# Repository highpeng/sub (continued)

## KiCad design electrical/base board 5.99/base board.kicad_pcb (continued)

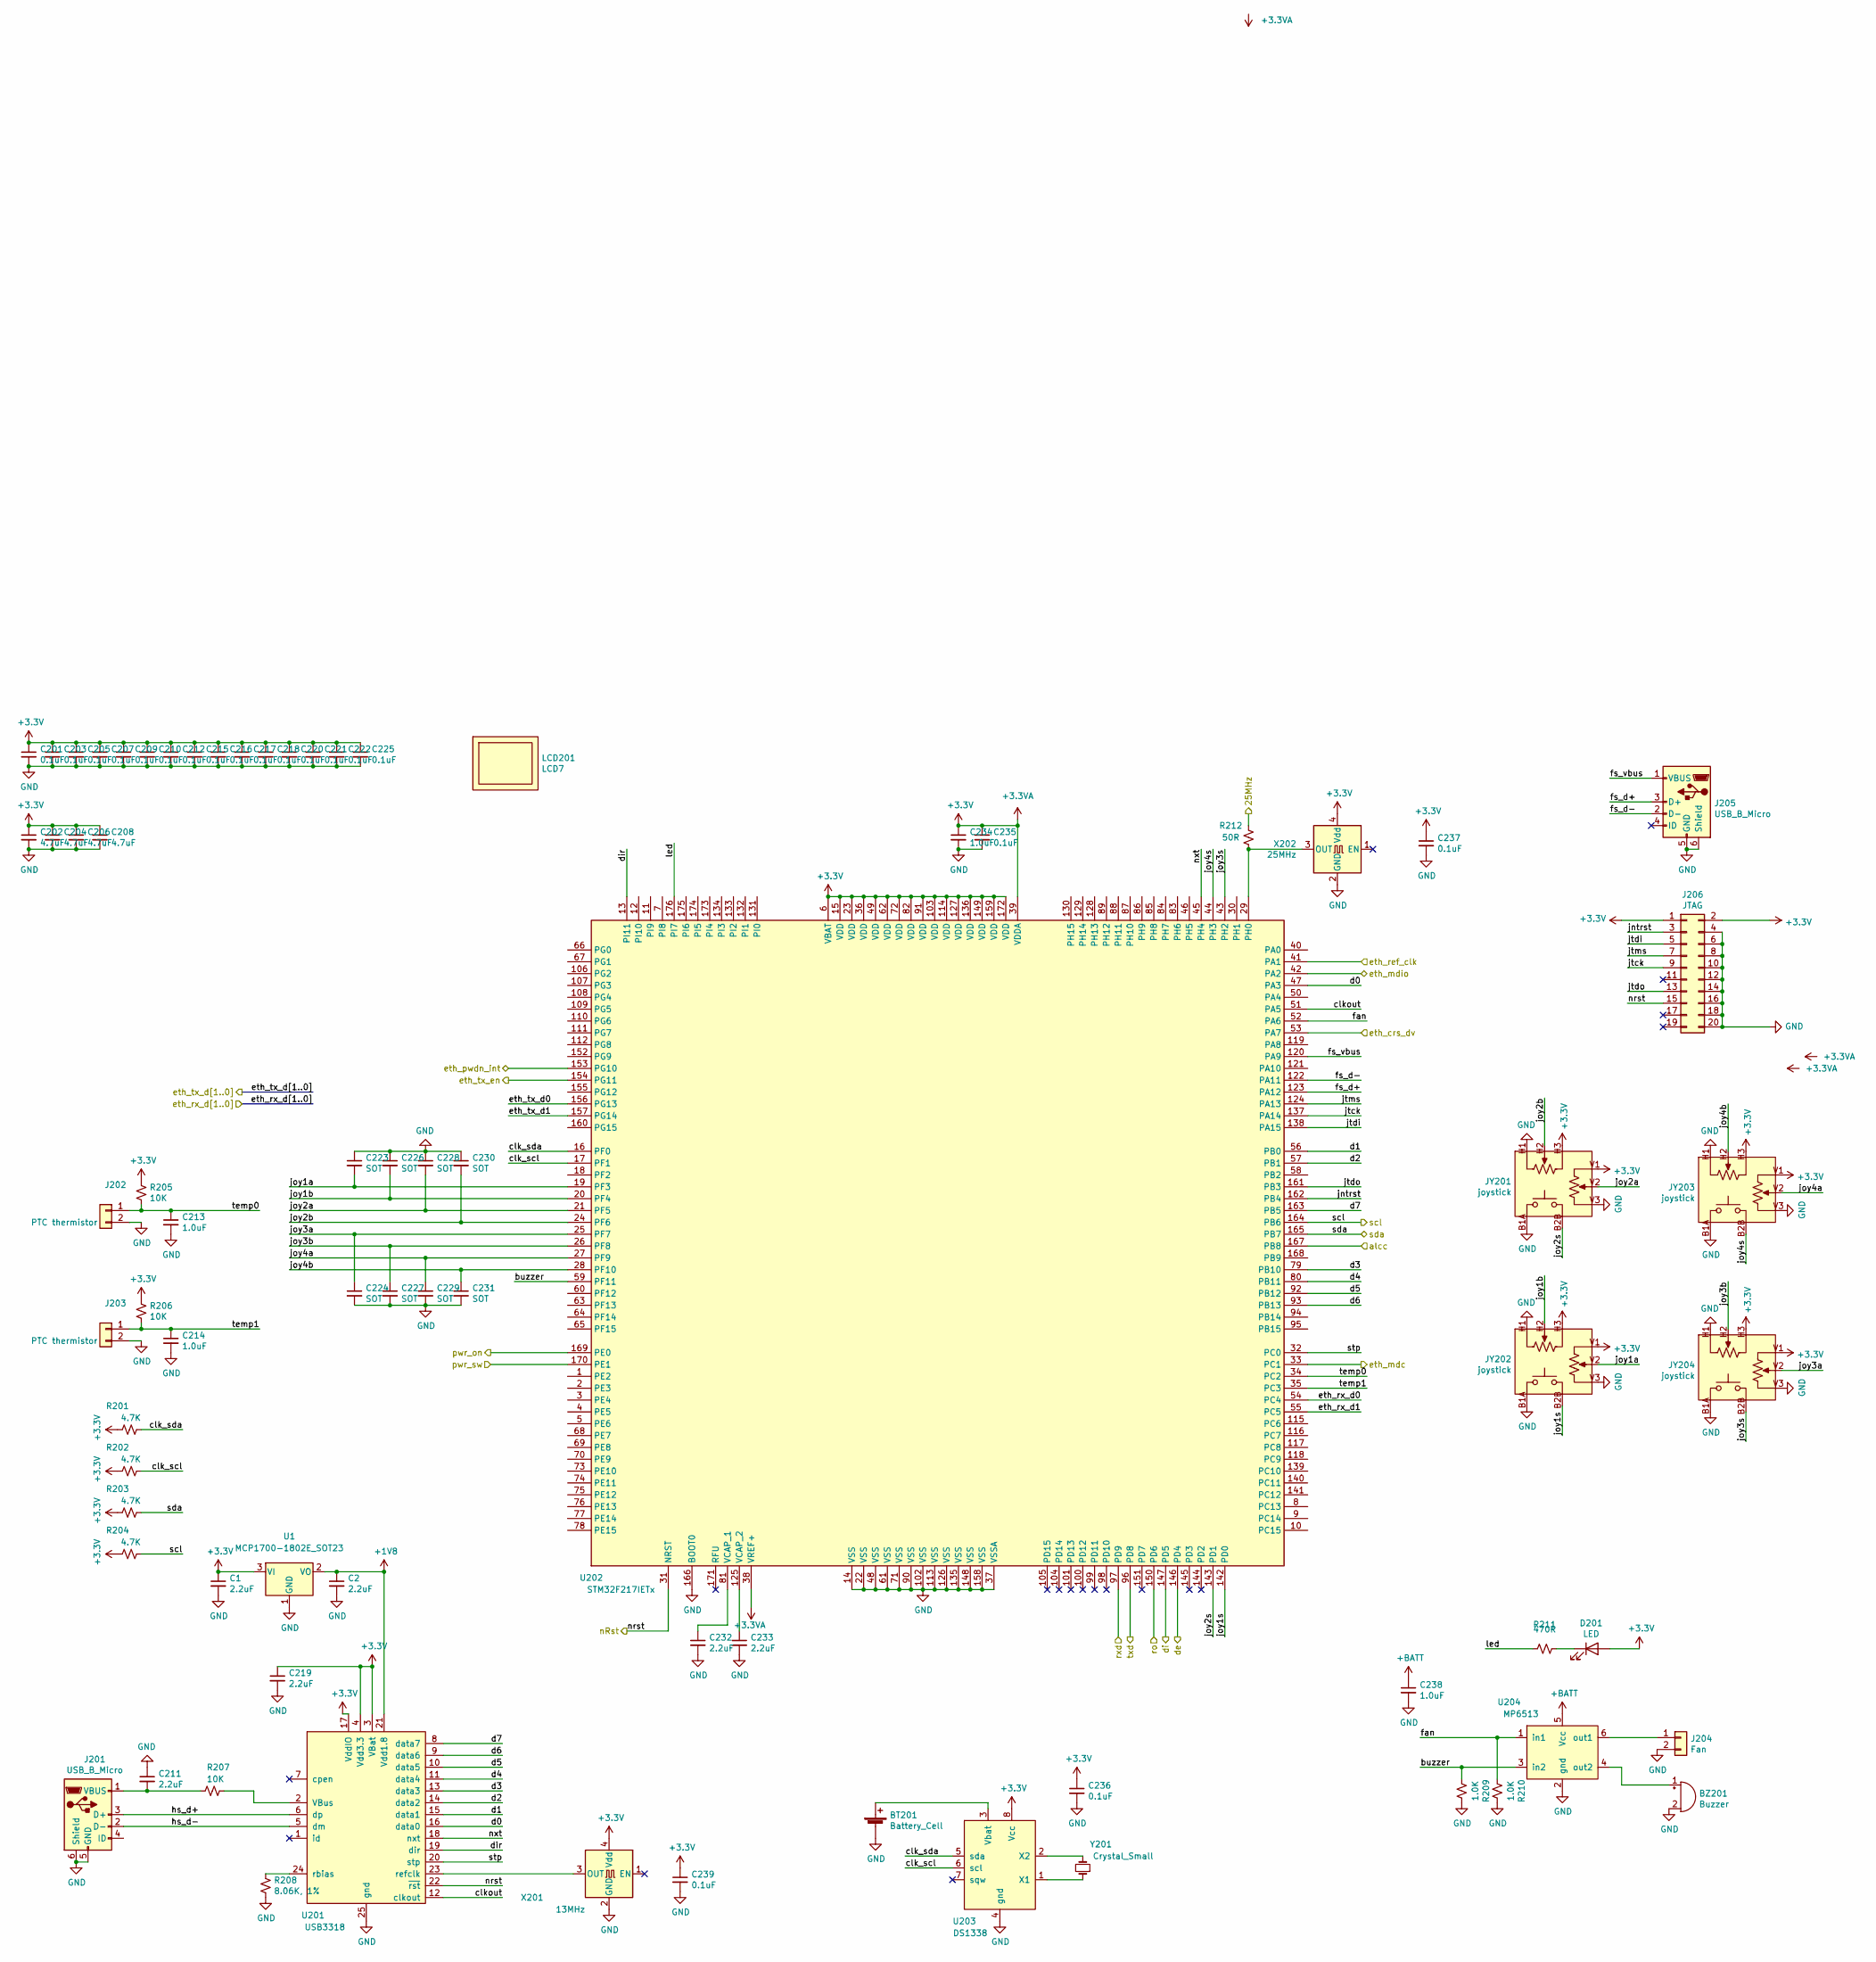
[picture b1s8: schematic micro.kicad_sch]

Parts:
BT201: Battery_Cell; BH-49C-1-BK
BZ201: Buzzer; CPI-1375-80T
C1, C2, C211, C219, C232, C233: 2.2uF; C_0603_1608Metric
C201, C203, C205, C207, C209, C210, C212, C215, C216, C217, C218, C220, C221, C222, C225, C235, C236, C237, C239: 0.1uF; C_0402_1005Metric
C202, C204, C206, C208: 4.7uF; C_0603_1608Metric
C213, C214, C234, C238: 1.0uF; C_0603_1608Metric
C223, C224, C226, C227, C228, C229, C230, C231: SOT; C_0402_1005Metric
D201: LED; LED_0402_1005Metric
J201, J205: USB_B_Micro; USB_Micro-B_Wuerth_629105150521
J202, J203: PTC thermistor; Hirose_DF13C_CL535-0402-2-51_1x02-1MP_P1.25mm_Vertical
J204: Fan; Hirose_DF13C_CL535-0402-2-51_1x02-1MP_P1.25mm_Vertical
J206: JTAG; IDC-Header_2x10_P2.54mm_Vertical
JY201, JY202, JY203, JY204: joystick; XDCR_COM-09032
LCD201: LCD7
R201, R202, R203, R204: 4.7K; R_0402_1005Metric
R205, R206, R207: 10K; R_0402_1005Metric
R208: 8.06K, 1%; R_0402_1005Metric
R209, R210: 1.0K; R_0402_1005Metric
R211: 470R; R_0402_1005Metric
R212: 50R; R_0402_1005Metric
U1: MCP1700-1802E_SOT23; SOT-23
U201: USB3318; QFN-24-1EP_4x4mm_P0.5mm_EP2.6x2.6mm
U202: STM32F217IETx; LQFP-176_24x24mm_P0.5mm
U203: DS1338; SOIC-8_3.9x4.9mm_P1.27mm
U204: MP6513; TSOT-23-6
X201: 13MHz; 831056290
X202: 25MHz; ASFL1
Y201: Crystal_Small; CMJ206T

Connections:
+1V8: C2.1, U1.2 (VO), U201.21 (Vdd1.8)
+3V3: C1.1, C201.1, C202.1, C203.1, C204.1, C205.1, C206.1, C207.1, C208.1, C209.1, C210.1, C212.1, C215.1, C216.1, C217.1, C218.1, C219.1, C220.1, C221.1, C222.1, C225.1, C234.1, C235.1, C236.1, C237.1, C239.1, D201.2 (A), J206.1, J206.2, JY201.H3, JY201.V1, JY202.H3, JY202.V1, JY203.H3, JY203.V1, JY204.H3, JY204.V1, R201.1, R202.1, R203.1, R204.1, R205.1, R206.1, U1.3 (VI), U201.3 (VBat~), U201.4 (Vdd3.3), U201.17 (VddIO), U202.6 (VBAT), U202.15 (VDD), U202.23 (VDD), U202.36 (VDD), U202.38 (VREF+), U202.39 (VDDA), U202.49 (VDD), U202.62 (VDD), U202.72 (VDD), U202.82 (VDD), U202.91 (VDD), U202.103 (VDD), U202.114 (VDD), U202.127 (VDD), U202.136 (VDD), U202.149 (VDD), U202.159 (VDD), U202.172 (VDD), U203.8 (Vcc), X201.4 (Vdd), X202.4 (Vdd); also elsewhere on the board
+BATT: C238.1, U204.5 (Vcc); also elsewhere on the board
/RS485/DE: U202.146 (PD4); also elsewhere on the board
/RS485/DI: U202.147 (PD5); also elsewhere on the board
/RS485/RO: U202.150 (PD6); also elsewhere on the board
/RaspberryPI_CM4/rxd: U202.96 (PD8); also elsewhere on the board
/RaspberryPI_CM4/txd: U202.97 (PD9); also elsewhere on the board
/battery/alcc: U202.167 (PB8); also elsewhere on the board
/battery/pwr_sw: U202.170 (PE1); also elsewhere on the board
/battery/scl: R204.2, U202.164 (PB6); also elsewhere on the board
/battery/sda: R203.2, U202.165 (PB7); also elsewhere on the board
/battery/st_pwr_en: U202.169 (PE0); also elsewhere on the board
/ethernet/25MHz: R212.2; also elsewhere on the board
/ethernet/50MHz: U202.41 (PA1); also elsewhere on the board
/ethernet/crs_dv: U202.53 (PA7); also elsewhere on the board
/ethernet/mdc: U202.33 (PC1); also elsewhere on the board
/ethernet/mdio: U202.42 (PA2); also elsewhere on the board
/ethernet/pwdn_int: U202.153 (PG10); also elsewhere on the board
/ethernet/tx_en: U202.154 (PG11); also elsewhere on the board
/micro/buzzer: R209.2, U202.59 (PF11), U204.3 (in2)
/micro/clk_scl: R202.2, U202.17 (PF1), U203.6 (scl)
/micro/clk_sda: R201.2, U202.16 (PF0), U203.5 (sda)
/micro/clkout: U201.12 (clkout), U202.51 (PA5)
/micro/d0: U201.16 (data0), U202.47 (PA3)
/micro/d1: U201.15 (data1), U202.56 (PB0)
/micro/d2: U201.14 (data2), U202.57 (PB1)
/micro/d3: U201.13 (data3), U202.79 (PB10)
/micro/d4: U201.11 (data4), U202.80 (PB11)
/micro/d5: U201.10 (data5), U202.92 (PB12)
/micro/d6: U201.9 (data6), U202.93 (PB13)
/micro/d7: U201.8 (data7), U202.163 (PB5)
/micro/dir: U201.19 (dir), U202.13 (PI11)
/micro/eth_rx_d0: U202.54 (PC4); also elsewhere on the board
/micro/eth_rx_d1: U202.55 (PC5); also elsewhere on the board
/micro/eth_tx_d0: U202.156 (PG13); also elsewhere on the board
/micro/eth_tx_d1: U202.157 (PG14); also elsewhere on the board
/micro/fan: R210.2, U202.52 (PA6), U204.1 (in1)
/micro/fs_d+: J205.3 (D+), U202.123 (PA12)
/micro/fs_d-: J205.2 (D-), U202.122 (PA11)
/micro/fs_vbus: J205.1 (VBUS), U202.120 (PA9)
/micro/hs_d+: J201.3 (D+), U201.6 (dp)
/micro/hs_d-: J201.2 (D-), U201.5 (dm)
/micro/jntrst: J206.3, U202.162 (PB4)
/micro/joy1a: C223.2, JY202.V2, U202.19 (PF3)
/micro/joy1b: C226.2, JY202.H2, U202.20 (PF4)
/micro/joy1s: JY202.B2B, U202.142 (PD0)
/micro/joy2a: C228.2, JY201.V2, U202.21 (PF5)
/micro/joy2b: C230.2, JY201.H2, U202.24 (PF6)
/micro/joy2s: JY201.B2B, U202.143 (PD1)
/micro/joy3a: C224.1, JY204.V2, U202.25 (PF7)
/micro/joy3b: C227.1, JY204.H2, U202.26 (PF8)
/micro/joy3s: JY204.B2B, U202.43 (PH2)
/micro/joy4a: C229.1, JY203.V2, U202.27 (PF9)
/micro/joy4b: C231.1, JY203.H2, U202.28 (PF10)
/micro/joy4s: JY203.B2B, U202.44 (PH3)
/micro/jtck: J206.9, U202.137 (PA14)
/micro/jtdi: J206.5, U202.138 (PA15)
/micro/jtdo: J206.13, U202.161 (PB3)
/micro/jtms: J206.7, U202.124 (PA13)
/micro/led: R211.2, U202.176 (PI7)
/micro/nrst: J206.15, U201.22 (~rst), U202.31 (NRST); also elsewhere on the board
/micro/nxt: U201.18 (nxt), U202.45 (PH4)
/micro/stp: U201.20 (stp), U202.32 (PC0)
/micro/temp0: C213.1, J202.1, R205.2, U202.34 (PC2)
/micro/temp1: C214.1, J203.1, R206.2, U202.35 (PC3)
GND: BT201.2 (-), BZ201.2 (+), C1.2, C2.2, C201.2, C202.2, C203.2, C204.2, C205.2, C206.2, C207.2, C208.2, C209.2, C210.2, C211.1, C212.2, C213.2, C214.2, C215.2, C216.2, C217.2, C218.2, C219.2, C220.2, C221.2, C222.2, C223.1, C224.2, C225.2, C226.1, C227.2, C228.1, C229.2, C230.1, C231.2, C232.2, C233.2, C234.2, C235.2, C236.2, C237.2, C238.2, C239.2, J201.5 (GND), J201.6 (Shield), J202.2, J203.2, J204.2, J205.5 (GND), J205.6 (Shield), J206.4, J206.6, J206.8, J206.10, J206.12, J206.14, J206.16, J206.18, J206.20, JY201.B1A, JY201.H1, JY201.V3, JY202.B1A, JY202.H1, JY202.V3, JY203.B1A, JY203.H1, JY203.V3, JY204.B1A, JY204.H1, JY204.V3, R208.1, R209.1, R210.1, U1.1 (GND), U201.25 (gnd), U202.14 (VSS), U202.22 (VSS), U202.37 (VSSA), U202.48 (VSS), U202.61 (VSS), U202.71 (VSS), U202.90 (VSS), U202.102 (VSS), U202.113 (VSS), U202.126 (VSS), U202.135 (VSS), U202.148 (VSS), U202.158 (VSS), U202.166 (BOOT0), U203.4 (gnd), U204.2 (gnd), X201.2 (GND), X202.2 (GND); also elsewhere on the board
unnamed: BT201.1 (+), U203.3 (Vbat)
unnamed: BZ201.1 (-), U204.4 (out2)
unnamed: C211.2, J201.1 (VBUS), R207.2
unnamed: C232.1, U202.81 (VCAP_1)
unnamed: C233.1, U202.125 (VCAP_2)
unnamed: J204.1, U204.6 (out1)
unnamed: R207.1, U201.2 (VBus)
unnamed: R208.2, U201.24 (rbias)
unnamed: D201.1 (K), R211.1
unnamed: R212.1, U202.29 (PH0), X202.3 (OUT)
unnamed: U201.23 (refclk), X201.3 (OUT)
unnamed: U203.1 (X1), Y201.1
unnamed: U203.2 (X2), Y201.2

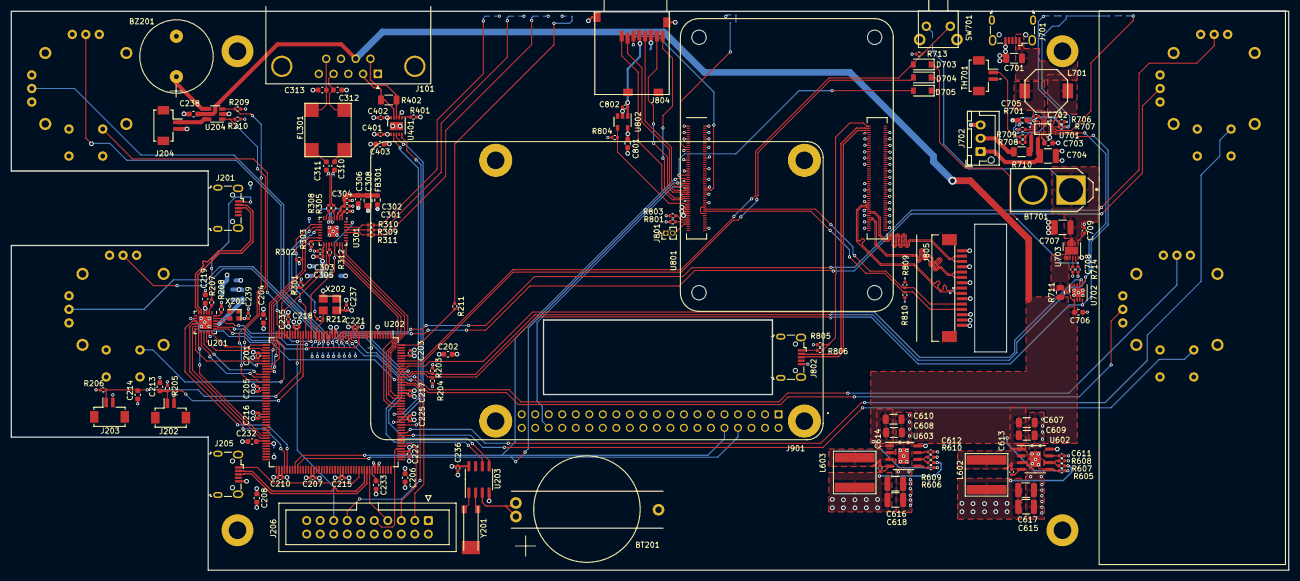
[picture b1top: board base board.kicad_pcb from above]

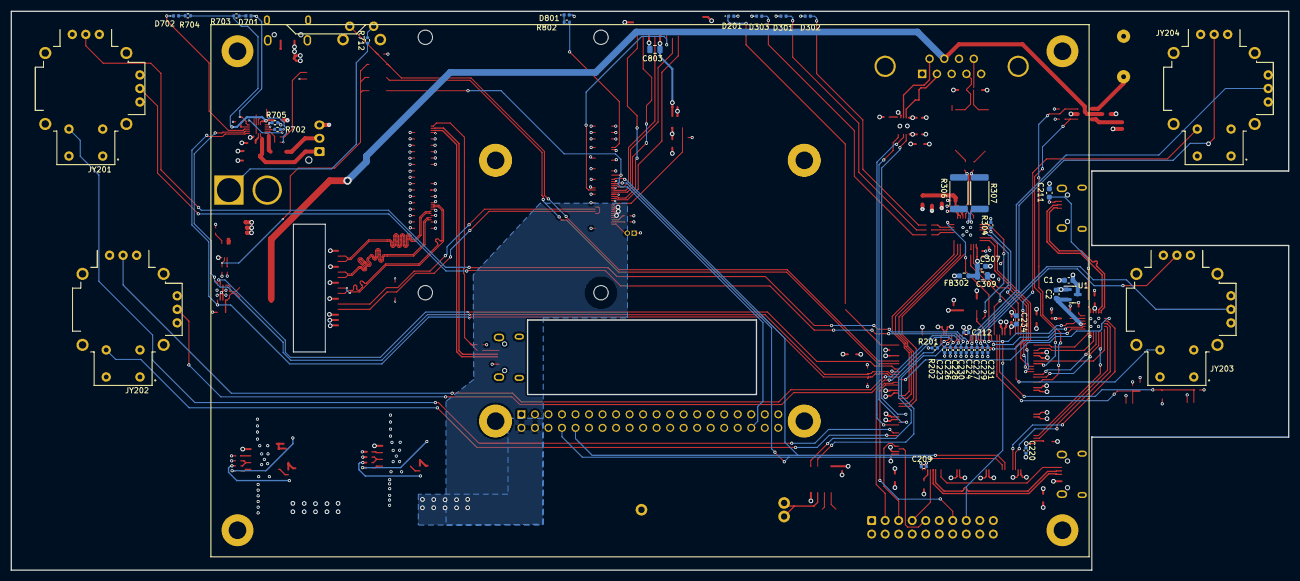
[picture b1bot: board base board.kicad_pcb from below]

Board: 4 copper layers, 240.0 x 105.0 mm, 193 parts (43 on the bottom side), 164 nets.

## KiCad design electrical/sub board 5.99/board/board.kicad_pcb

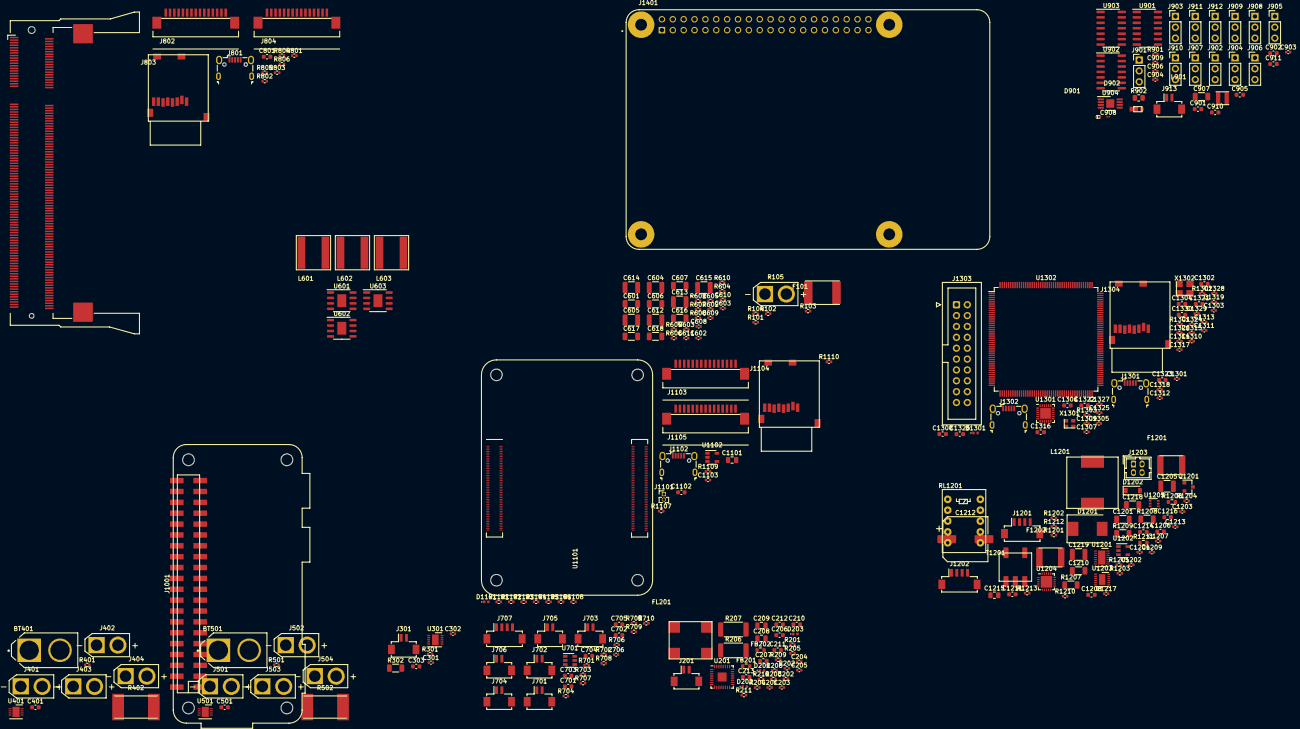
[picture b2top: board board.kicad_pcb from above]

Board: 2 copper layers, 279 parts (0 on the bottom side), 260 nets, no tracks yet.

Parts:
BT401, BT501: Battery; AMASS_XT60-M
C201, C202, C203, C909: 10nF, 16V; C_0402_1005Metric
C204, C205, C301, C302, C602, C603, C608, C609, C610, C611, C706, C903, C904, C906, C1103, C1202, C1301, C1303, C1305, C1307, C1309, C1310, C1311, C1312, C1313, C1314, C1315, C1317, C1318, C1319, C1320, C1324, C1325, C1327, C1328, C1329: 0.1uF; C_0402_1005Metric
C206, C207, C303, C705, C801, C901, C902, C905, C1206, C1208, C1302, C1304, C1306, C1308, C1330: 4.7uF; C_0603_1608Metric
C208, C209, C1101: 10uF; C_0805_2012Metric
C210, C211: 220nF,16V; C_0603_1608Metric
C212, C213: 100pF, 50V; C_0603_1608Metric
C401, C501, C701, C702, C703, C704, C910, C911, C1102, C1323: 1.0uF, 16V; C_0603_1608Metric
C601, C606, C607, C616, C617, C618, C907, C1201, C1218: 10uF,25V; C_1206_3216Metric
C604, C605, C612, C613, C614, C615: 22uF; C_1210_3225Metric
C908: 0.1uF,25V; C_01005_0402Metric
C1203: 33nF; C_0402_1005Metric
C1204, C1213: 6.8nF; C_0402_1005Metric
C1205, C1219: 10uF, 63V, X7R; C_1210_3225Metric
C1207, C1209: 1nF; C_0402_1005Metric
C1210: 0.1uF, 63V; C_1206_3216Metric
C1211, C1214: SOT; C_0603_1608Metric
C1212: 100uF, 63V; CP_MS10
C1215: 330pF, 100V; R_0805_2012Metric
C1216: NIP; C_0603_1608Metric
C1217: SOT; C_0402_1005Metric
C1316, C1321, C1322, C1326: 2.2uF; C_0603_1608Metric
D201, D202, D203, D1101, D1301: LED; LED_0402_1005Metric
D901: RB720M-30; SOD-923
D902: 30V, 1A; DO-219AD
D1201: 50V,4A; D_SMC
D1202: 1N4148; D_SOD-123
F101: 6A; 2920L
F1201, F1202: 3A; 2016
FB201, FB202: FB; R_0603_1608Metric
FL201: 2.2mH; L_WE_SL5
J201: Ethernet; Hirose_DF13C_CL535-0402-2-51_1x02-1MP_P1.25mm_Vertical
J301: RS485; Hirose_DF13C_CL535-0402-2-51_1x02-1MP_P1.25mm_Vertical
J401, J402, J403, J404, J501, J502, J503, J504: thruster_esc; AMASS_XT30U-F_1x02_P5.0mm_Vertical
J701, J702, J703, J704: PTC thermistor; Hirose_DF13C_CL535-0402-2-51_1x02-1MP_P1.25mm_Vertical
J705: water sensor0; Hirose_DF13C_CL535-0402-2-51_1x02-1MP_P1.25mm_Vertical
J706: water sensor1; Hirose_DF13C_CL535-0402-2-51_1x02-1MP_P1.25mm_Vertical
J707: IMU; Hirose_DF13C_CL535-0404-8-51_1x04-1MP_P1.25mm_Vertical
J801, J1102, J1301, J1302: USB_B_Micro; USB_Micro-B_Wuerth_629105150521
J802, J1103: Cam0; Molex_200528-0150_1x15-1MP_P1.00mm_Horizontal
J803, J1104, J1304: Micro_SD_Card_Det; MEM2061
J804, J1105: Cam1; Molex_200528-0150_1x15-1MP_P1.00mm_Horizontal
J901: thruster_esc0; PinHeader_1x03_P2.54mm_Vertical
J902: thruster_esc1; PinHeader_1x03_P2.54mm_Vertical
J903: thruster_esc2; PinHeader_1x03_P2.54mm_Vertical
J904: thruster_esc3; PinHeader_1x03_P2.54mm_Vertical
J905: thruster_esc4; PinHeader_1x03_P2.54mm_Vertical
J906: thruster_esc5; PinHeader_1x03_P2.54mm_Vertical
J907: thruster_esc6; PinHeader_1x03_P2.54mm_Vertical
J908: thruster_esc7; PinHeader_1x03_P2.54mm_Vertical
J909: servo0; PinHeader_1x03_P2.54mm_Vertical
J910: servo1; PinHeader_1x03_P2.54mm_Vertical
J911: servo2; PinHeader_1x03_P2.54mm_Vertical
J912: servo3; PinHeader_1x03_P2.54mm_Vertical
J913: LED; Hirose_DF13C_CL535-0402-2-51_1x02-1MP_P1.25mm_Vertical
J1001: Raspberry_Pi; Raspberry_Pi_Zero_Socketed_THT_MountingHoles_SMT
J1101: nRPIBoot; PinHeader_1x02_P1.27mm_Vertical
J1201: barometer; Hirose_DF13C_CL535-0404-8-51_1x04-1MP_P1.25mm_Vertical
J1202: lidar; Hirose_DF13C_CL535-0404-8-51_1x04-1MP_P1.25mm_Vertical
J1203: Transducers; Hirose_DF11-4DP-2DSA_2x02_P2.00mm_Vertical
J1303: JTAG; IDC-Header_2x10_P2.54mm_Vertical
J1401: Raspberry_Pi; MODULE_RASPBERRY_PI_3_MODEL_B+
L601: 2.0uH; NR8040
L602: 3.6uH; NR8040
L603: 4.7uH; NR8040
L901: 6.8uH, 1.5A; L_TDK_VLS3012
L1201: 13.3uH, 4A; L_7447706150
Q1201: 2N7002K; SOT-23
R101, R102, R103, R104, R401, R501, R801, R802, R1201: 4.7K; R_0402_1005Metric
R105: 0R; AMASS_XT30U-F_1x02_P5.0mm_Vertical
R201, R202, R203, R204, R1105, R1107: 2.2K; R_0402_1005Metric
R205, R208: 50R; R_0402_1005Metric
R206, R207: 2K; R_2512_6332Metric
R209, R210, R211, R1210, R1212, R1302: 470R; R_0402_1005Metric
R301, R1203: 40K; R_0402_1005Metric
R302: 120R; R_1206_3216Metric
R402, R502: 0m5; R_Shunt_Yaego_PU3921
R601, R605, R606: 100K; R_0402_1005Metric
R602: 30K; R_0402_1005Metric
R603: 5.0K; R_0402_1005Metric
R604: 4.07K; R_0402_1005Metric
R607, R609: 75K; R_0402_1005Metric
R608: 24.32K; R_0402_1005Metric
R610: 14.46K; R_0402_1005Metric
R701, R702, R703, R704, R901, R1205, R1303: 10K; R_0402_1005Metric
R705, R707: 1.0M; R_0402_1005Metric
R706, R708, R709, R710, R1102, R1213: 1.0K; R_0402_1005Metric
R803, R804, R805, R806, R1104, R1106, R1108, R1109, R1110: 1.8K; R_0402_1005Metric
R902: 0R2, 0.5W; R_0805_2012Metric
R1101, R1103: DNP; R_0402_1005Metric
R1202: 66.5K; R_0402_1005Metric
R1204: 276K; R_0402_1005Metric
R1206: 10R; R_0603_1608Metric
R1207, R1208: NIP; R_1206_3216Metric
R1209: 3K, 1/4W; R_1206_3216Metric
R1211: NIP; R_0603_1608Metric
R1301: 8.06K, 1%; R_0402_1005Metric
RL1201: EA2-5NJ
T1201: B78416A2232A003; XFRMR_B78416
U201: DP83TD510E; TQFN-32-1EP_5x5mm_P0.5mm_EP2.1x2.1mm
U301: MAX22500E; DFN-10-1EP_3x3mm_P0.5mm_EP1.55x2.48mm
U401, U501: LTC2943; DFN-8-1EP_3x3mm_P0.5mm_EP1.66x2.38mm
U601, U602, U603: RT7263A; SOP-EP-8_3.9x4.9mm_P1.27mm
U701: TLV4082; SOT-23-6
U801: RaspberryPi-CM3+L; Conn_TE-DDR2-SODIMM-0.6-200P-doublesided
U901, U902, U903: 74HCT125; SO-14_3.9x8.65mm_P1.27mm
U904: LM3405A; VSSOP-8_3.0x3.0mm_P0.65mm-EP
U1101: Compute_Module_4_Connectors; CM4
U1102: AP22814AW5; SOT-23-5
U1201: MP3426; DFN-14-1EP_3x4mm_P0.5mm_EP1.7x3.3mm
U1202: ADP165; SOT-23-5
U1203: AOZ13984DI-02; DFN-12-1EP_3x3mm_P0.5mm_EP1.5x2.5mm
U1204: TUSS44x0; WQFN-20
U1205: 74LVC2G17; SOT-363_SC-70-6
U1301: USB3318; QFN-24-1EP_4x4mm_P0.5mm_EP2.6x2.6mm
U1302: STM32F217IETx; LQFP-176_24x24mm_P0.5mm
X1301: 13MHz; 831056290
X1302: 25MHz; ASFL1

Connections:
+1V8: C604.1, C605.1, C1328.2, L601.2, R603.1, U801.183, U801.184, U801.185, U801.186, U1301.21
+3V3: BT401.2, BT501.2, C201.2, C202.2, C203.2, C204.2, C205.2, C206.2, C207.2, C208.2, C209.2, C212.2, C213.1, C301.1, C301.2, C302.1, C302.2, C303.1, C303.2, C401.2, C501.2, C601.2, C602.2, C604.2, C605.2, C606.2, C607.2, C608.2, C609.2, C612.1, C612.2, C613.2, C614.1, C614.2, C615.2, C616.2, C617.2, C618.2, C701.2, C702.2, C703.2, C704.2, C705.1, C705.2, C706.1, C706.2, C801.1, C801.2, C901.2, C902.2, C903.2, C904.2, C905.2, C906.2, C907.2, C908.2, C910.2, C1101.1, C1102.1, C1102.2, C1103.1, C1201.2, C1202.2, C1203.2, C1204.2, C1205.2, C1206.2, C1207.2, C1208.2, C1209.2, C1210.2, C1211.1, C1212.2, C1213.2, C1214.1, C1217.2, C1218.2, C1219.2, C1301.1, C1301.2, C1302.1, C1302.2, C1303.1, C1303.2, C1304.1, C1304.2, C1305.1, C1305.2, C1306.1, C1306.2, C1307.1, C1307.2, C1308.1, C1308.2, C1309.1, C1309.2, C1310.1, C1310.2, C1311.1, C1311.2, C1312.1, C1312.2, C1313.1, C1313.2, C1314.1, C1314.2, C1315.1, C1315.2, C1316.2, C1317.1, C1317.2, C1318.1, C1318.2, C1319.1, C1319.2, C1320.1, C1320.2, C1321.2, C1322.2, C1323.1, C1323.2, C1324.1, C1324.2, C1325.1, C1325.2, C1326.1, C1327.1, C1327.2, C1328.1, C1329.1, C1329.2, C1330.1, C1330.2, D902.2, D1101.2, F1202.2, FB201.1, FB202.1, J401.2, J402.2, J403.2, J404.2, J501.2, J502.2, J503.2, J504.2, J701.2, J702.2, J703.2, J704.2, J707.1, J707.4, J801.5, J801.6, J802.1, J802.4, J802.7, J802.10, J802.15, J803.4, J803.6, J803.11, J804.1, J804.4, J804.7, J804.10, J804.15, J901.3, J902.3, J903.3, J904.3, J905.3, J906.3, J907.3, J908.3, J909.3, J910.3, J911.3, J912.3, J1001.6, J1001.9, J1001.14, J1001.20, J1001.25, J1001.30, J1001.34, J1001.39, J1101.1, J1102.5, J1102.6, J1103.1, J1103.4, J1103.7, J1103.10, J1103.15, J1104.6, J1104.11, J1105.1, J1105.4, J1105.7, J1105.10, J1105.15, J1201.4, J1202.2, J1301.5, J1301.6, J1302.5, J1302.6, J1303.1, J1303.2, J1303.4, J1303.6, J1303.8, J1303.10, J1303.12, J1303.14, J1303.16, J1303.18, J1303.20, J1304.4, J1304.6, J1304.11, J1401.6, J1401.9, J1401.14, J1401.20, J1401.25, J1401.30, J1401.34, J1401.39, L602.2, Q1201.2, R101.2, R102.2, R103.2, R104.2, R201.2, R202.2, R203.1, R204.2, R209.1, R210.1, R211.1, R301.2, R401.2, R501.2, R604.2, R607.1, R608.2, R610.2, R701.1, R702.1, R703.1, R704.1, R705.2, R706.1, R707.2, R708.1, R801.2, R802.2, R803.1, R804.1, R805.1, R806.1, R901.2, R902.2, R1101.2, R1103.2, R1104.2, R1105.2, R1106.1, R1108.1, R1109.1, R1110.1, R1201.1, R1202.1, R1205.1, R1301.1, R1302.1, U201.33, U301.1, U301.7, U301.10, U301.11, U401.2, U401.3, U401.7, U401.9, U501.2, U501.3, U501.7, U501.9, U601.8, U601.9, U602.8, U602.9, U603.8, U603.9, U701.1, U701.5, U801.1, U801.4, U801.6, U801.7, U801.8, U801.13, U801.14, U801.19, U801.20, U801.25, U801.26, U801.31, U801.32, U801.37, U801.38, U801.39, U801.40, U801.41, U801.42, U801.43, U801.44, U801.49, U801.50, U801.55, U801.56, U801.61, U801.62, U801.67, U801.68, U801.73, U801.74, U801.79, U801.80, U801.85, U801.86, U801.91, U801.92, U801.97, U801.98, U801.103, U801.104, U801.109, U801.110, U801.115, U801.116, U801.121, U801.122, U801.127, U801.133, U801.134, U801.139, U801.140, U801.145, U801.146, U801.151, U801.152, U801.157, U801.163, U801.164, U801.168, U801.169, U801.170, U801.181, U801.182, U801.187, U801.188, U801.191, U801.192, U801.193, U801.194, U801.195, U801.196, U901.1, U901.4, U901.7, U901.10, U901.13, U902.1, U902.4, U902.7, U902.10, U902.13, U903.1, U903.4, U903.7, U903.10, U903.13, U904.2, U904.7, U904.9, U1101.1, U1101.2, U1101.7, U1101.8, U1101.13, U1101.14, U1101.22, U1101.23, U1101.32, U1101.33, U1101.42, U1101.43, U1101.52, U1101.53, U1101.59, U1101.60, U1101.65, U1101.66, U1101.71, U1101.74, U1101.98, U1101.107, U1101.108, U1101.113, U1101.114, U1101.119, U1101.120, U1101.125, U1101.126, U1101.131, U1101.132, U1101.137, U1101.138, U1101.144, U1101.150, U1101.155, U1101.156, U1101.161, U1101.162, U1101.167, U1101.168, U1101.173, U1101.174, U1101.179, U1101.180, U1101.185, U1101.186, U1101.191, U1101.192, U1101.197, U1101.198, U1102.2, U1102.5, U1201.8, U1201.9, U1201.10, U1201.11, U1201.15, U1202.2, U1203.6, U1204.2, U1204.13, U1204.14, U1205.2, U1205.5, U1301.3, U1301.17, U1301.25, U1302.6, U1302.14, U1302.15, U1302.22, U1302.23, U1302.36, U1302.37, U1302.39, U1302.48, U1302.49, U1302.61, U1302.62, U1302.71, U1302.72, U1302.82, U1302.90, U1302.91, U1302.102, U1302.103, U1302.113, U1302.114, U1302.126, U1302.127, U1302.135, U1302.136, U1302.148, U1302.149, U1302.158, U1302.159, U1302.166, U1302.172, X1301.2, X1301.4, X1302.2, X1302.4
+5V: C613.1, C615.1, C901.1, C902.1, C903.1, C904.1, C905.1, C906.1, C1206.1, D901.2, D1202.1, J801.1, J1001.2, J1001.4, J1401.2, J1401.4, L603.2, R609.1, RL1201.1, U801.197, U801.198, U801.199, U801.200, U901.14, U902.14, U903.14, U1101.77, U1101.79, U1101.81, U1101.83, U1101.85, U1101.87, U1202.1, U1202.3
+BATT: C601.1, C606.1, C607.1, C616.1, C617.1, C618.1, C907.1, C908.1, C1201.1, C1207.1, C1218.1, F101.1, L1201.1, R601.1, R605.1, R606.1, U601.1, U602.1, U603.1, U904.6, U1201.3, U1203.9, U1203.10
/ESC_servo_lights/5V_1: J901.2, J909.2
/ESC_servo_lights/5V_2: J902.2, J910.2
/ESC_servo_lights/5V_3: J903.2, J911.2
/ESC_servo_lights/5V_4: J904.2, J912.2
/ESC_servo_lights/bldc1: U901.5, U1302.101
/ESC_servo_lights/bldc2: U901.9, U1302.104
/ESC_servo_lights/bldc3: U901.12, U1302.105
/ESC_servo_lights/bldc5: U902.5, U1302.88
/ESC_servo_lights/bldc6: U902.9, U1302.89
/ESC_servo_lights/bldc7: U902.12, U1302.131
/ESC_servo_lights/servo1: U903.5, U1302.74
/ESC_servo_lights/servo2: U903.9, U1302.76
/ESC_servo_lights/servo3: U903.12, U1302.77
/RS485/DE: U301.3, U301.4, U1302.146
/RS485/DI: U301.5, U1302.147
/RS485/RO: U301.2, U1302.150
/RaspberryPIZero/rxd: J1001.10, J1401.10, U801.53, U1101.34, U1101.51, U1302.96
/RaspberryPiCM3+/cam0_cn: J802.8, U801.144
/RaspberryPiCM3+/cam0_cp: J802.9, U801.142
/RaspberryPiCM3+/cam0_dn0: J802.2, U801.138
/RaspberryPiCM3+/cam0_dn1: J802.5, U801.150
/RaspberryPiCM3+/cam0_dp0: J802.3, U801.136
/RaspberryPiCM3+/cam0_dp1: J802.6, U801.148
/RaspberryPiCM3+/cam0_io0: J802.11, U801.36
/RaspberryPiCM3+/cam0_io1: J802.12, U801.34
/RaspberryPiCM3+/cam1_cn: J804.8, U801.149
/RaspberryPiCM3+/cam1_cp: J804.9, U801.147
/RaspberryPiCM3+/cam1_dn0: J804.2, U801.161
/RaspberryPiCM3+/cam1_dn1: J804.5, U801.155
/RaspberryPiCM3+/cam1_dp0: J804.3, U801.159
/RaspberryPiCM3+/cam1_dp1: J804.6, U801.153
/RaspberryPiCM3+/cam1_io0: J804.11, U801.11
/RaspberryPiCM3+/cam1_io1: J804.12, U801.9
/RaspberryPiCM3+/cd0_scl: J802.13, R803.2, U801.30
/RaspberryPiCM3+/cd0_sda: J802.14, R804.2, U801.28
/RaspberryPiCM3+/cd1_scl: J804.13, R805.2, U801.5
/RaspberryPiCM3+/cd1_sda: J804.14, R806.2, U801.3
/RaspberryPiCM3+/sd_clk: J803.5, U801.10
/RaspberryPiCM3+/sd_cmd: J803.3, U801.12
/RaspberryPiCM3+/sd_dat0: J803.7, U801.16
/RaspberryPiCM3+/sd_dat1: J803.8, U801.18
/RaspberryPiCM3+/sd_dat2: J803.1, U801.22
/RaspberryPiCM3+/sd_dat3: J803.2, U801.24
/RaspberryPiCM4/cam0_cn: J1103.8, U1101.140
/RaspberryPiCM4/cam0_cp: J1103.9, U1101.142
/RaspberryPiCM4/cam0_dn0: J1103.2, U1101.128
/RaspberryPiCM4/cam0_dn1: J1103.5, U1101.134
/RaspberryPiCM4/cam0_dp0: J1103.3, U1101.130
/RaspberryPiCM4/cam0_dp1: J1103.6, U1101.136
/RaspberryPiCM4/cam1_cn: J1105.8, U1101.127
/RaspberryPiCM4/cam1_cp: J1105.9, U1101.129
/RaspberryPiCM4/cam1_dn0: J1105.2, U1101.115
/RaspberryPiCM4/cam1_dn1: J1105.5, U1101.121
/RaspberryPiCM4/cam1_dp0: J1105.3, U1101.117
/RaspberryPiCM4/cam1_dp1: J1105.6, U1101.123
/RaspberryPiCM4/cam_gpio: J1103.11, J1105.11, U1101.97
/RaspberryPiCM4/cd0_scl: J1103.13, R1106.2, U1101.35
/RaspberryPiCM4/cd0_sda: J1103.14, R1108.2, U1101.36
/RaspberryPiCM4/cd1_scl: J1105.13, R1109.2, U1101.80
/RaspberryPiCM4/cd1_sda: J1105.14, R1110.2, U1101.82
/RaspberryPiCM4/sd_clk: J1104.5, U1101.57
/RaspberryPiCM4/sd_cmd: J1104.3, U1101.62
/RaspberryPiCM4/sd_dat0: J1104.7, U1101.63
/RaspberryPiCM4/sd_dat1: J1104.8, U1101.67
/RaspberryPiCM4/sd_dat2: J1104.1, U1101.69
/RaspberryPiCM4/sd_dat3: J1104.2, U1101.61
/RaspberryPiCM4/sd_pwr_on: R1104.1, U1101.75, U1102.4
/RaspberryPiCM4/usb_d+: J1102.3, U1101.105
/RaspberryPiCM4/usb_d-: J1102.2, U1101.103
/RaspberryPiCM4/usb_otg: R1105.1, R1107.1, U1101.101
/battery/Vbatt: C401.1, F101.2, J401.1, J402.1, J403.1, J404.1, R105.1, R402.1, U401.1
/battery/alcc: R401.1, U401.6, U1302.19
/ethernet/50MHz: U201.19, U1302.41
/ethernet/crs_dv: R201.1, U201.18, U1302.53
/ethernet/rx_d0: R203.2, U201.16
/ethernet/rx_d1: R202.1, U201.15
/internal_sensors/temp0: C701.1, J701.1, R701.2, U1302.24
/internal_sensors/temp1: C702.1, J702.1, R702.2, U1302.25
/internal_sensors/temp2: C703.1, J703.1, R703.2, U1302.26
/internal_sensors/temp3: C704.1, J704.1, R704.2, U1302.27
/internal_sensors/water: U701.2, U701.3, U1302.18
/lights: R901.1, U904.8, U1302.4
/micro/clkout: U1301.12, U1302.51
/micro/d0: U1301.16, U1302.47
/micro/d1: U1301.15, U1302.56
/micro/d2: U1301.14, U1302.57
/micro/d3: U1301.13, U1302.79
/micro/d4: U1301.11, U1302.80
/micro/d5: U1301.10, U1302.92
/micro/d6: U1301.9, U1302.93
/micro/d7: U1301.8, U1302.163
/micro/dir: U1301.19, U1302.13
/micro/eth_mdc: U201.12, U1302.33
/micro/eth_mdio: R204.1, U201.11, U1302.42
/micro/eth_pwdn_int: U201.21, U1302.153
/micro/eth_tx_en: U201.23, U1302.154
/micro/fs_dm: J1302.2, U1302.122
/micro/fs_dp: J1302.3, U1302.123
/micro/fs_vbus: J1302.1, U1302.120
/micro/jntrst: J1303.3, U1302.162
/micro/jtck: J1303.9, U1302.137
/micro/jtdi: J1303.5, U1302.138
/micro/jtdo: J1303.13, U1302.161
/micro/jtms: J1303.7, U1302.124
/micro/led: D1301.1, U1302.10
/micro/lidar_pwr: U1205.1, U1302.165
/micro/lidar_rx: U1205.4, U1302.121
/micro/nRst: J1303.15, U201.31, U1301.22, U1302.31
/micro/nxt: U1301.18, U1302.45
/micro/rxd: J1001.8, J1401.8, U801.51, U1101.54, U1101.55, U1302.97
/micro/sd_cd: J1304.9, U1302.8
/micro/sd_clk: J1304.5, U1302.141
/micro/sd_cmd: J1304.3, U1302.144
/micro/sd_dat0: J1304.7, U1302.117
/micro/sd_dat1: J1304.8, U1302.118
/micro/sd_dat2: J1304.1, U1302.139
/micro/sd_dat3: J1304.2, U1302.140
/micro/sonar_ana_in: U1204.9, U1302.34
/micro/sonar_clk: U1204.8, U1302.83, U1302.167
/micro/sonar_io1: U1204.7, U1302.173
/micro/sonar_out3: U1204.1, U1302.115
/micro/sonar_out4: U1204.19, U1302.116
/micro/sonar_pwr: R1201.2, U1201.2, U1302.175
/micro/sonar_sel: R1213.2, U1302.174
/micro/stp: U1301.20, U1302.32
/scl0: R101.1, U401.4, U1302.84
/scl1: J707.3, J1201.2, R103.1, U501.4, U1302.17
/sda0: R102.1, U401.5, U1302.85
/sda1: J707.2, J1201.3, R104.1, U501.5, U1302.16
/sheet6168BB46/Vbatt: C501.1, J501.1, J502.1, J503.1, J504.1, R105.2, R502.1, U501.1
/sheet6168BB46/alcc: R501.1, U501.6, U1302.20
/water_sensors/lidar_pwr: U1203.5, U1302.164
/water_sensors/sonar_ncs: U1204.3, U1302.168
/water_sensors/sonar_sclk: U1204.4, U1302.132
/water_sensors/sonar_sdi: U1204.5, U1302.95
/water_sensors/sonar_sdo: U1204.6, U1302.94
unnamed: BT401.1, R402.2, U401.8
unnamed: BT501.1, R502.2, U501.8
unnamed: C201.1, U201.1, U201.2
unnamed: C202.1, C204.1, C206.1, C208.1, FB201.2, U201.3
unnamed: C203.1, C205.1, C207.1, C209.1, FB202.2, U201.17
unnamed: C210.1, FL201.2
unnamed: C210.2, R205.1, R206.1
unnamed: C211.1, FL201.1
unnamed: C211.2, R207.1, R208.1
unnamed: C212.1, FL201.3, J201.1
unnamed: C213.2, FL201.4, J201.2
unnamed: C602.1, U601.7
unnamed: C603.1, U601.4
unnamed: C603.2, L601.1, U601.2, U601.3
unnamed: C608.1, U602.7
unnamed: C609.1, U603.7
unnamed: C610.1, U602.4
unnamed: C610.2, L602.1, U602.2, U602.3
unnamed: C611.1, U603.4
unnamed: C611.2, L603.1, U603.2, U603.3
unnamed: C909.1, D901.1, U904.4
unnamed: C909.2, D902.1, L901.1, U904.5
unnamed: C910.1, C911.1, J913.1, L901.2
unnamed: C911.2, J913.2, R902.1, U904.1
unnamed: C1101.2, C1103.2, J1104.4, U1102.1
unnamed: C1202.1, U1201.7
unnamed: C1203.1, U1201.12
unnamed: C1204.1, R1203.1
unnamed: C1205.1, C1219.1, D1201.1, R1204.2, R1206.2
unnamed: C1208.1, U1202.5, U1204.10
unnamed: C1209.1, U1203.4
unnamed: C1210.1, R1206.1, U1204.20
unnamed: C1211.2, U1204.18
unnamed: C1212.1, T1201.2, U1204.17
unnamed: C1213.1, U1203.7
unnamed: C1214.2, U1204.11
unnamed: C1215.1, R1209.1
unnamed: C1215.2, U1204.12
unnamed: C1216.1, R1207.1, R1211.1, RL1201.8, T1201.5
unnamed: C1216.2, R1208.1, R1211.2, RL1201.3, T1201.4
unnamed: C1217.1, R1212.2, U1205.3
unnamed: C1316.1, U1301.4
unnamed: C1321.1, U1302.81
unnamed: C1322.1, U1302.125
unnamed: C1326.2, J1301.1, R1303.2
unnamed: D201.1, R209.2
unnamed: D201.2, U201.29
unnamed: D202.1, R210.2
unnamed: D202.2, U201.30
unnamed: D203.1, R211.2
unnamed: D203.2, U201.28
unnamed: D1101.1, R1102.2
unnamed: D1201.2, L1201.2, U1201.4, U1201.5, U1201.6
unnamed: D1202.2, Q1201.3, RL1201.10
unnamed: D1301.2, R1302.2
unnamed: F1201.1, J1202.1
unnamed: F1201.2, U1203.1, U1203.2
unnamed: F1202.1, J1201.1
unnamed: J301.1, R302.1, U301.8
unnamed: J301.2, R302.2, U301.9
unnamed: J705.1, R705.1, R709.1
unnamed: J705.2, R706.2
unnamed: J706.1, R707.1, R710.2
unnamed: J706.2, R708.2
unnamed: J801.2, U801.167
unnamed: J801.3, U801.165
unnamed: J901.1, U901.3
unnamed: J902.1, U901.6
unnamed: J903.1, U901.8
unnamed: J904.1, U901.11
unnamed: J905.1, U902.3
unnamed: J906.1, U902.6
unnamed: J907.1, U902.8
unnamed: J908.1, U902.11
unnamed: J909.1, U903.3
unnamed: J910.1, U903.6
unnamed: J911.1, U903.8
unnamed: J912.1, U903.11
unnamed: J1101.2, U1101.93
unnamed: J1102.1, R1107.2
unnamed: J1202.3, R1212.1
unnamed: J1202.4, R1210.1
unnamed: J1203.1, RL1201.7
unnamed: J1203.2, R1209.2, RL1201.9
unnamed: J1203.3, RL1201.2
unnamed: J1203.4, RL1201.4
unnamed: J1301.2, U1301.5
unnamed: J1301.3, U1301.6
unnamed: Q1201.1, R1213.1
unnamed: R205.2, U201.4
unnamed: R206.2, U201.5
unnamed: R207.2, U201.6
unnamed: R208.2, U201.7
unnamed: R301.1, U301.6
unnamed: R601.2, U601.5
unnamed: R602.1, R603.2, R604.1
unnamed: R602.2, U601.6
unnamed: R605.2, U602.5
unnamed: R606.2, U603.5
unnamed: R607.2, R608.1, U602.6
unnamed: R609.2, R610.1, U603.6
unnamed: R709.2, U701.6
unnamed: R710.1, U701.4
unnamed: R801.1, U801.84
unnamed: R802.1, U801.82
unnamed: R1101.1, U1101.91
unnamed: R1102.1, U1101.21
unnamed: R1103.1, U1101.89
unnamed: R1202.2, U1201.14
unnamed: R1203.2, U1201.1
unnamed: R1204.1, R1205.2, U1201.13
unnamed: R1207.2, T1201.1, U1204.15
unnamed: R1208.2, T1201.3, U1204.16
unnamed: R1210.2, U1205.6
unnamed: R1301.2, U1301.24
unnamed: R1303.1, U1301.2
unnamed: U801.189, U801.190
unnamed: U1101.78, U1101.84
unnamed: U1301.23, X1301.3
unnamed: U1302.29, X1302.3

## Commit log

2021-10-14 updated sub board
2021-10-24 base board layout
